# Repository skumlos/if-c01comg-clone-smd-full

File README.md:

IF-C01COMG Clone board SMD Full size

This is a full sized version of the IF-C01COMG board for JVC pro monitors (TM-Hxx50CG) and some others...

It's basically the THT base board I made some months ago, with most components changed to SMD.

Credit goes to James Vanderloeff for the dual input idea.

Board is for now completely untested...

Finally this is a Kicad 5.1 project :D

You're welcome to clone, sell, re-design and whatever, see LICENSE.

(2021) Martin Hejnfelt (martin@hejnfelt.com)
This work is free. You can redistribute it and/or modify it under the
terms of the Do What The Fuck You Want To Public License, Version 2,
as published by Sam Hocevar. See the LICENSE file for more details.

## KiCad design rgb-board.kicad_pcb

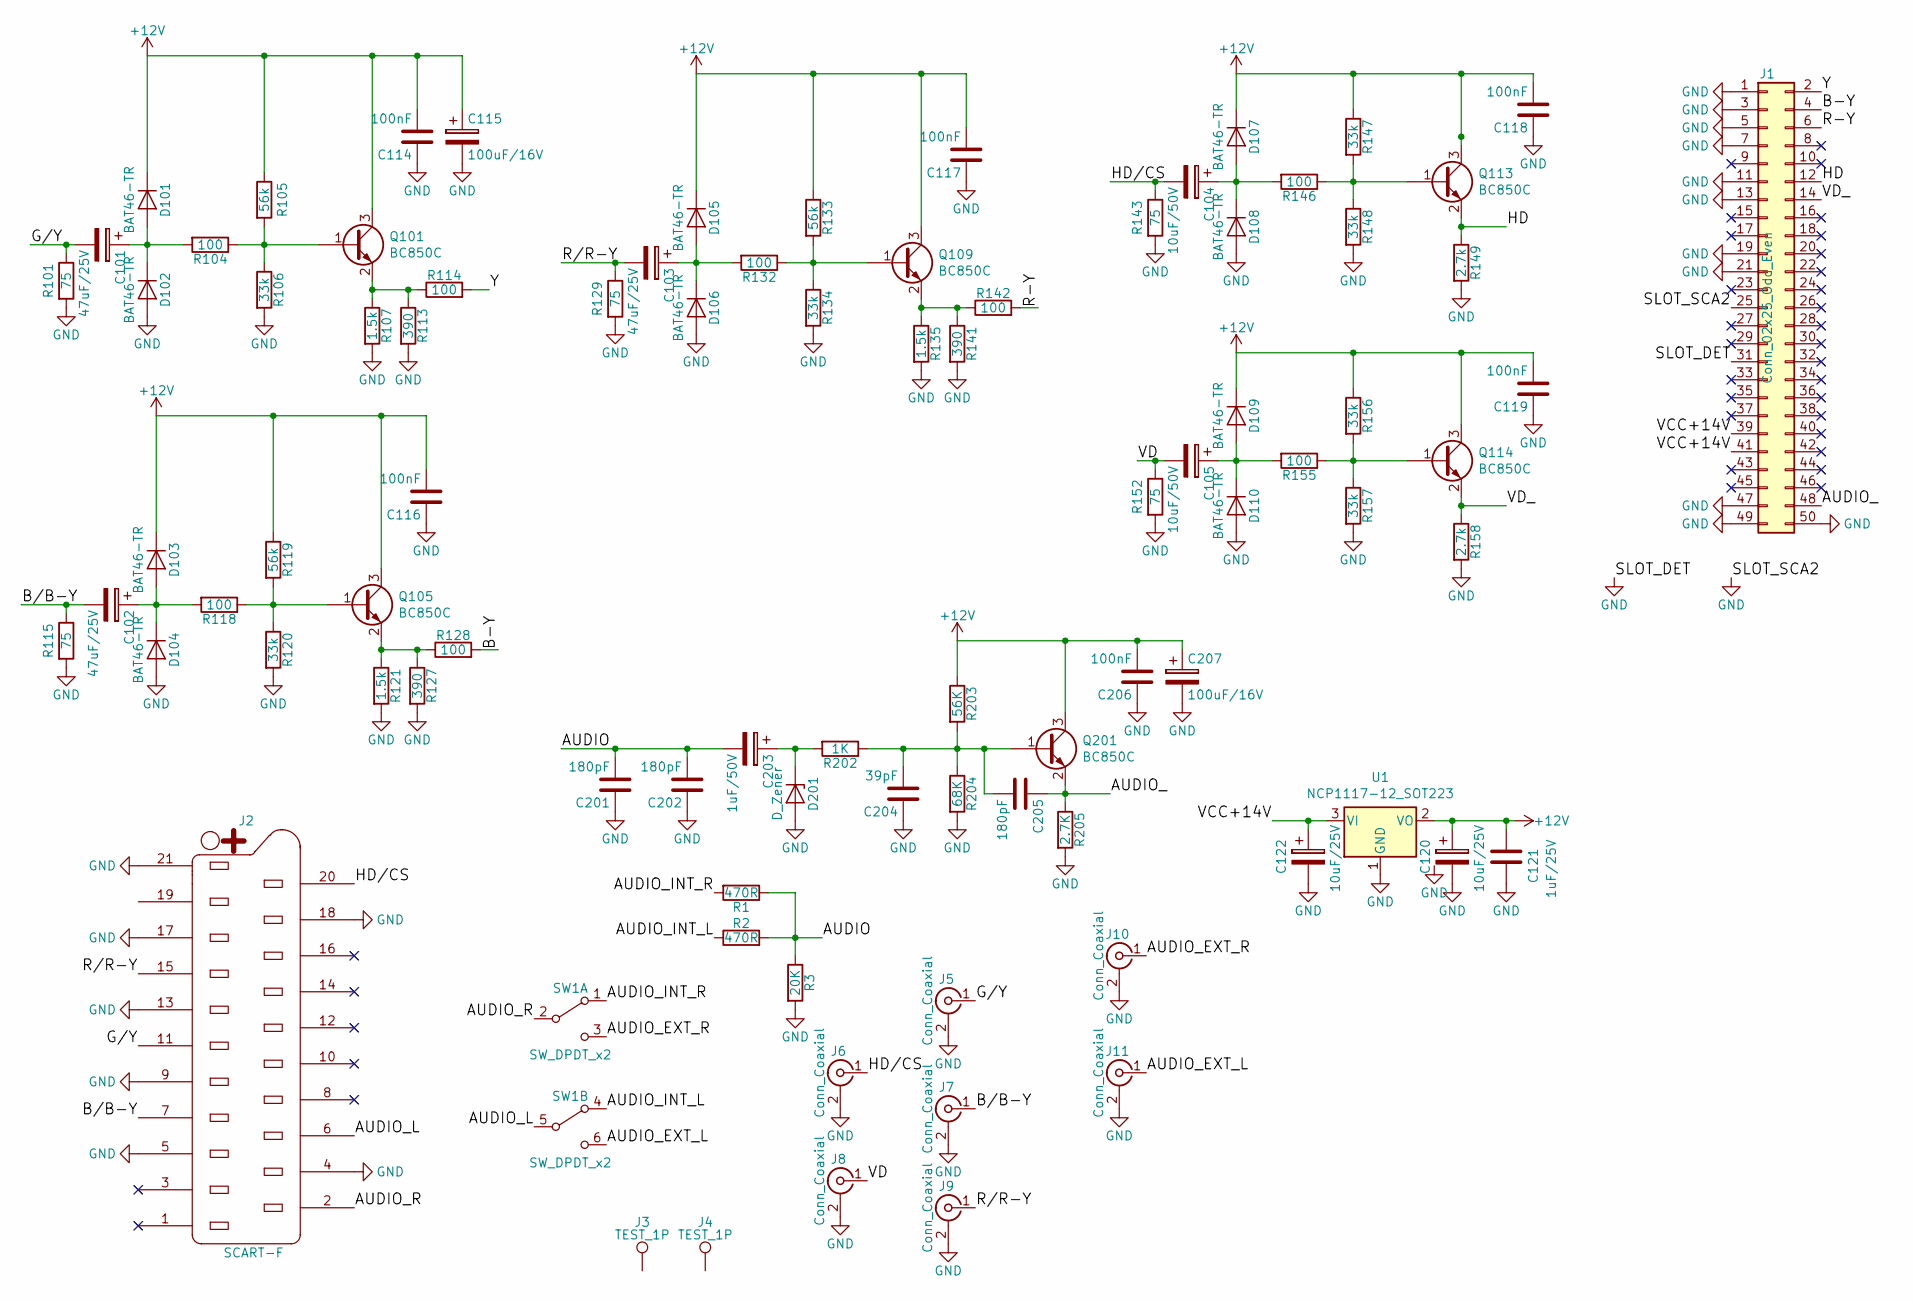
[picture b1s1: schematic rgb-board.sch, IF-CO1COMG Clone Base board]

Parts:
C101, C102, C103: 47uF/25V; C_Elec_6.3x5.4
C104, C105: 10uF/50V; C_Elec_5x5.4
C114, C116, C117, C118, C119, C206: 100nF; C_0805_2012Metric_Pad1.18x1.45mm_HandSolder
C115, C207: 100uF/16V; C_Elec_6.3x5.4
C120, C122: 10uF/25V; C_Elec_5x5.4
C121: 1uF/25V; C_0805_2012Metric_Pad1.18x1.45mm_HandSolder
C201, C202, C205: 180pF; C_0805_2012Metric_Pad1.18x1.45mm_HandSolder
C203: 1uF/50V; C_Elec_4x5.4
C204: 39pF; C_0805_2012Metric_Pad1.18x1.45mm_HandSolder
D101, D102, D103, D104, D105, D106, D107, D108, D109, D110: BAT46-TR; D_SOD-123
D201: D_Zener; D_SOD-123
J1: Conn_02x25_Odd_Even; Pin_Header_Angled_2x25_Pitch2.54mm
J2: SCART-F; NINIGI-SCART-RA
J3, J4: TEST_1P; MountingHole_3.2mm_M3
J5, J6, J7, J8, J9: Conn_Coaxial; BNC-THT
J10, J11: Conn_Coaxial; RCJ-04X
Q101, Q105, Q109, Q113, Q114, Q201: BC850C; SOT-23_Handsoldering
R1, R2: 470R; R_0805_2012Metric_Pad1.20x1.40mm_HandSolder
R3: 20K; R_0805_2012Metric_Pad1.20x1.40mm_HandSolder
R101, R115, R129, R143, R152: 75; R_0805_2012Metric_Pad1.20x1.40mm_HandSolder
R104, R114, R118, R128, R132, R142, R146, R155: 100; R_0805_2012Metric_Pad1.20x1.40mm_HandSolder
R105, R119, R133: 56k; R_0805_2012Metric_Pad1.20x1.40mm_HandSolder
R106, R120, R134, R147, R148, R156, R157: 33k; R_0805_2012Metric_Pad1.20x1.40mm_HandSolder
R107, R121, R135: 1.5k; R_0805_2012Metric_Pad1.20x1.40mm_HandSolder
R113, R127, R141: 390; R_0805_2012Metric_Pad1.20x1.40mm_HandSolder
R149, R158: 2.7k; R_0805_2012Metric_Pad1.20x1.40mm_HandSolder
R202: 1K; R_0805_2012Metric_Pad1.20x1.40mm_HandSolder
R203: 56K; R_0805_2012Metric_Pad1.20x1.40mm_HandSolder
R204: 68K; R_0805_2012Metric_Pad1.20x1.40mm_HandSolder
R205: 2.7K; R_0805_2012Metric_Pad1.20x1.40mm_HandSolder
SW1: SW_DPDT_x2; LC2259
U1: NCP1117-12_SOT223; SOT-223-3_TabPin2

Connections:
+12V: C114.2, C115.1, C116.2, C117.2, C118.2, C119.2, C120.1, C121.2, C206.2, C207.1, D101.1 (K), D103.1 (K), D105.1 (K), D107.1 (K), D109.1 (K), Q101.3 (C), Q105.3 (C), Q109.3 (C), Q113.3 (C), Q114.3 (C), Q201.3 (C), R105.1, R119.1, R133.1, R147.1, R156.1, R203.1, U1.2 (VO)
/AUDIO: C201.2, C202.2, C203.2, R1.1, R2.2, R3.1
/AUDIO_: C205.1, J1.48, Q201.2 (E), R205.1
/AUDIO_EXT_L: J11.1 (In), SW1.6 (C)
/AUDIO_EXT_R: J10.1 (In), SW1.3 (C)
/AUDIO_INT_L: R2.1, SW1.4 (A)
/AUDIO_INT_R: R1.2, SW1.1 (A)
/AUDIO_L: J2.6, SW1.5 (B)
/AUDIO_R: J2.2, SW1.2 (B)
/B-Y: J1.4, R128.2
/B/B-Y: C102.2, J2.7, J7.1 (In), R115.1
/G/Y: C101.2, J2.11, J5.1 (In), R101.1
/HD: J1.12, Q113.2 (E), R149.1
/HD/CS: C104.2, J2.20, J6.1 (In), R143.1
/R-Y: J1.6, R142.2
/R/R-Y: C103.2, J2.15, J9.1 (In), R129.1
/VCC+14V: C122.1, J1.39, J1.41, U1.3 (VI)
/VD: C105.2, J8.1 (In), R152.1
/VD_: J1.14, Q114.2 (E), R158.1
/Y: J1.2, R114.2
GND: C114.1, C115.2, C116.1, C117.1, C118.1, C119.1, C120.2, C121.1, C122.2, C201.1, C202.1, C204.1, C206.1, C207.2, D102.2 (A), D104.2 (A), D106.2 (A), D108.2 (A), D110.2 (A), D201.2 (A), J1.1, J1.3, J1.5, J1.7, J1.11, J1.13, J1.19, J1.21, J1.25, J1.31, J1.47, J1.49, J1.50, J2.4, J2.5, J2.9, J2.13, J2.17, J2.18, J2.21, J5.2 (Ext), J6.2 (Ext), J7.2 (Ext), J8.2 (Ext), J9.2 (Ext), J10.2 (Ext), J11.2 (Ext), R3.2, R101.2, R106.2, R107.2, R113.2, R115.2, R120.2, R121.2, R127.2, R129.2, R134.2, R135.2, R141.2, R143.2, R148.2, R149.2, R152.2, R157.2, R158.2, R204.2, R205.2, U1.1 (GND)
unnamed: C101.1, D101.2 (A), D102.1 (K), R104.2
unnamed: C102.1, D103.2 (A), D104.1 (K), R118.2
unnamed: C103.1, D105.2 (A), D106.1 (K), R132.2
unnamed: C104.1, D107.2 (A), D108.1 (K), R146.2
unnamed: C105.1, D109.2 (A), D110.1 (K), R155.2
unnamed: C203.1, D201.1 (K), R202.2
unnamed: C204.2, C205.2, Q201.1 (B), R202.1, R203.2, R204.1
unnamed: Q101.1 (B), R104.1, R105.2, R106.1
unnamed: Q101.2 (E), R107.1, R113.1, R114.1
unnamed: Q105.1 (B), R118.1, R119.2, R120.1
unnamed: Q105.2 (E), R121.1, R127.1, R128.1
unnamed: Q109.1 (B), R132.1, R133.2, R134.1
unnamed: Q109.2 (E), R135.1, R141.1, R142.1
unnamed: Q113.1 (B), R146.1, R147.2, R148.1
unnamed: Q114.1 (B), R155.1, R156.2, R157.1

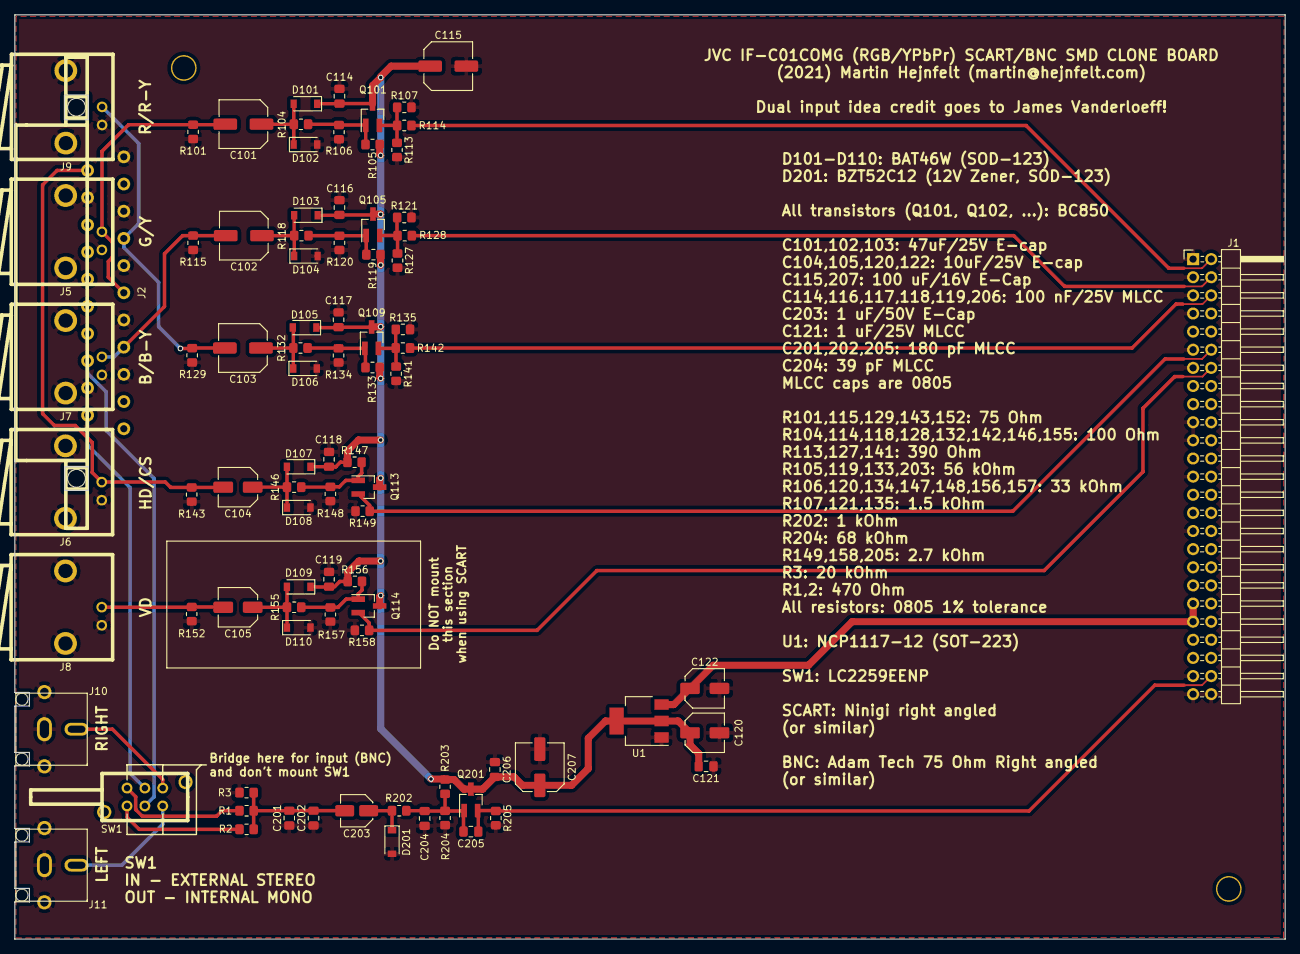
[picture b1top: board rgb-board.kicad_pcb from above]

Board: 2 copper layers, 178.0 x 129.5 mm, 89 parts (0 on the bottom side), 36 nets.
